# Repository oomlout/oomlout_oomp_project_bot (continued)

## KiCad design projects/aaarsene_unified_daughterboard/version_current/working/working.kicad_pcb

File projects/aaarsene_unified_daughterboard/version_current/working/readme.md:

# OOMP Project  
## Unified-Daughterboard  by aaarsene  
  
oomp key: oomp_projects_flat_aaarsene_unified_daughterboard  
(snippet of original readme)  
  
- Unified Daughterboard Project  

-- Introduction  
The Unified Daughterboard Project is an attempt by leading designers in the mechanical keyboard community to standardize the USB daughterboards used for their custom mechanical keyboard projects. It has initially been envisioned by users ai03, Wilba, Hineybush, Xelus, Xondat, aeryxz and Maximillian.  
  
The main characteristic of this daughterboard is to integrate a USB Type C connector and the needed circuitry for USB2.0 operation in a small PCB that can be screwed to a keyboard chassis; this significantly simplifies the assembly and design of the main circuit board.  
  
-- C3 version  
  
In its latest version, C3, this daughterboard features:  
  
* ESD (Electrostatic Discharge) protection on the data lines of the USB connector through a specialized chip;  
* Overcurrent protection through a PTC fuse;  
* Overvoltage protection through a bidirectional TVS diode;  
* Shielding noise decoupling capabilities through a ferrite bead;  
* Single-path grounding of the metallic chassis to which the daughterboard is attached.  
  
Adittionally, the C3 version is backwards compatible with both C1 and C2 versions since it has the same dimensions and us  
  full source readme at [readme_src.md](readme_src.md)  
  
source repo at: [https://github.com/aaarsene/Unified-Daughterboard](https://github.com/aaarsene/Unified-Daughterboard)  
## Board  

## Schematic  

[schematic pdf](working_schematic.pdf)  
## Images

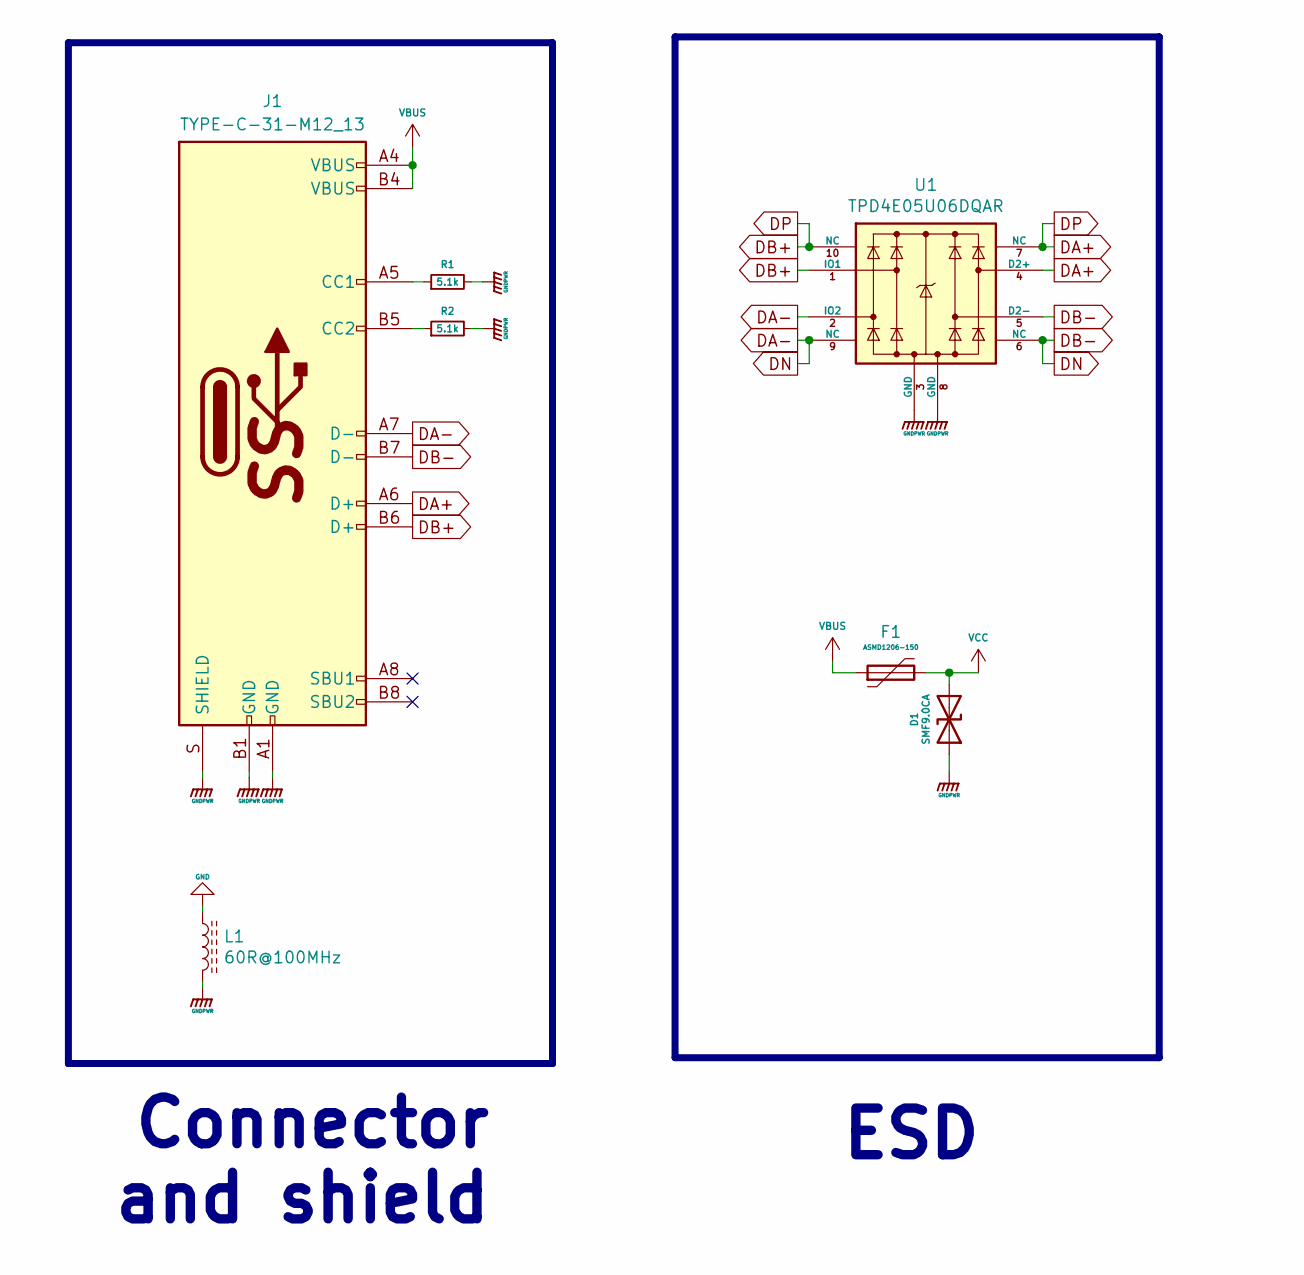
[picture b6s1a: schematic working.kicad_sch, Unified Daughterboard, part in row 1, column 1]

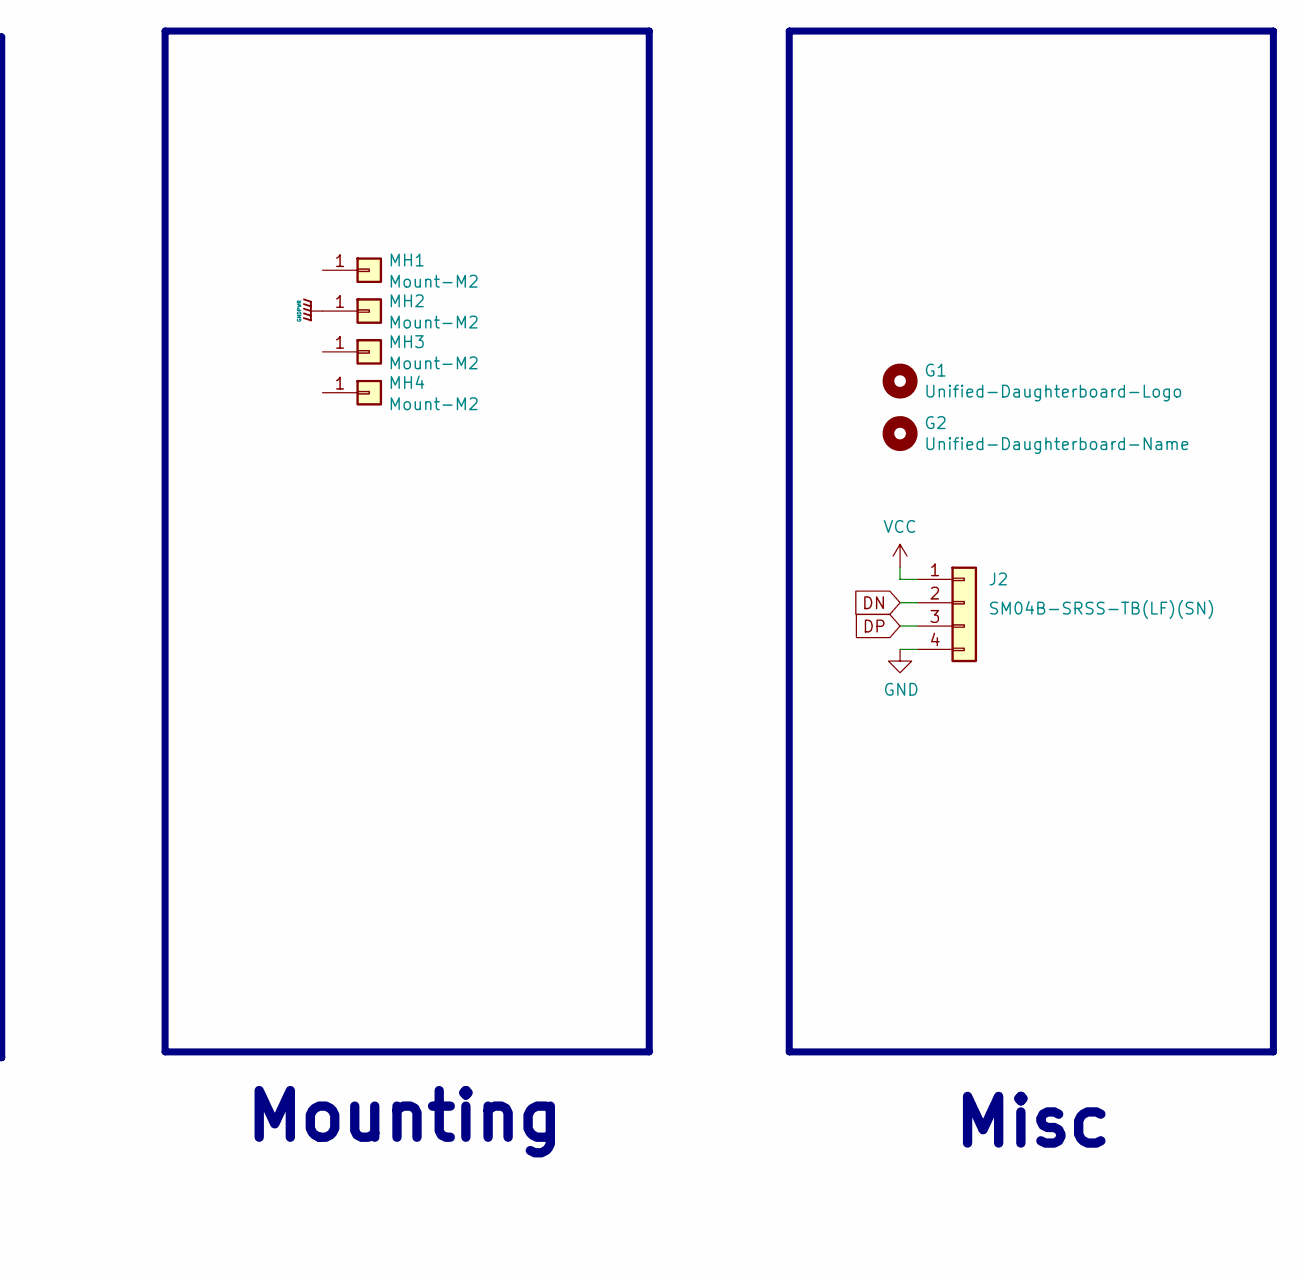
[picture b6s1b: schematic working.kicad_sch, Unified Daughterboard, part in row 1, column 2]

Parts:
D1: SMF9.0CA; D_SOD-123_Bidirectional; Manufacturer Part No SMF9.0CA; LCSC Part No C123799
F1: ASMD1206-150; Fuse_1206_3216Metric; Manufacturer Part No ASMD1206-150; LCSC Part No C135342
G1: Unified-Daughterboard-Logo; Unified-Daughterboard-Logo.pretty
G2: Unified-Daughterboard-Name; Unified-Daughterboard-Name.pretty
J1: TYPE-C-31-M12_13; TYPE-C-31-M-12; Manufacturer Part No TYPE-C-31-M-12; LCSC Part No C165948
J2: SM04B-SRSS-TB(LF)(SN); JST-SR-4; Manufacturer Part No SM04B-SRSS-TB(LF)(SN); LCSC Part No C160404
L1: 60R@100MHz; L_1206_3216Metric; Manufacturer Part No MLB3216-600P4A(f); LCSC Part No C33600
MH1, MH2, MH3, MH4: Mount-M2; Generic-Mounthole
R1, R2: 5.1k; R_0603
U1: TPD4E05U06DQAR; USON-10_2.5x1.0mm_P0.5mm; Manufacturer Part No TPD4E05U06DQAR; LCSC Part No C138714

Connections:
DA+: J1.A6 (D+), J1.B6 (D+), J2.3, U1.1 (IO1), U1.4 (D2+), U1.7 (NC), U1.10 (NC)
DA-: J1.A7 (D-), J1.B7 (D-), J2.2, U1.2 (IO2), U1.5 (D2-), U1.6 (NC), U1.9 (NC)
GND: J2.4, L1.1
GNDPWR: D1.1 (A1), J1.A1 (GND), J1.B1 (GND), J1.S (SHIELD), L1.2, MH2.1, R1.2, R2.2, U1.3 (GND), U1.8 (GND)
unnamed: J1.A5 (CC1), R1.1
unnamed: J1.B5 (CC2), R2.1
VBUS: F1.1, J1.A4 (VBUS), J1.B4 (VBUS)
VCC: D1.2 (A2), F1.2, J2.1

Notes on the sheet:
ESD
Misc
Connector and shield
Mounting

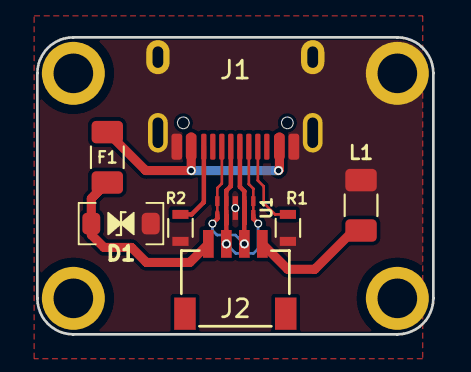
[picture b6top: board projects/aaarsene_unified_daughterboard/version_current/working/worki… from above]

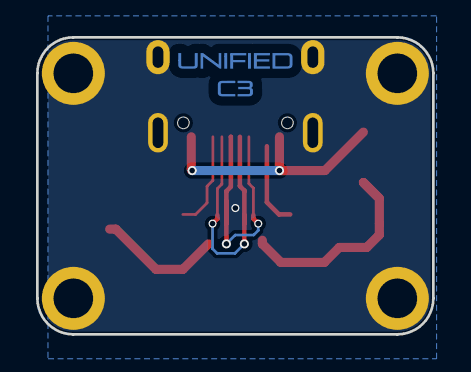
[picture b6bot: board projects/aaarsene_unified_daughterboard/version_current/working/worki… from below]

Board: 2 copper layers, 22.0 x 16.5 mm, 14 parts (2 on the bottom side), 8 nets.

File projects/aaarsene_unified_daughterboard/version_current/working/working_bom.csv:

"Id";"Designator";"Footprint";"Quantity";"Designation";"Supplier and ref";
1;"J1";"TYPE-C-31-M-12";1;"TYPE-C-31-M12_13";;;
2;"J2";"JST-SR-4";1;"SM04B-SRSS-TB(LF)(SN)";;;
3;"D1";"D_SOD-123_Bidirectional";1;"SMF9.0CA";;;
4;"F1";"Fuse_1206_3216Metric";1;"ASMD1206-150";;;
5;"U1";"USON-10_2.5x1.0mm_P0.5mm";1;"TPD4E05U06DQAR";;;
6;"R2,R1";"R_0603";2;"5.1k";;;
7;"L1";"L_1206_3216Metric";1;"60R@100MHz";;;
8;"G2";"Unified-Daughterboard-Name.pretty";1;"Unified-Daughterboard-Name";;;
9;"G1";"Unified-Daughterboard-Logo.pretty";1;"Unified-Daughterboard-Logo";;;

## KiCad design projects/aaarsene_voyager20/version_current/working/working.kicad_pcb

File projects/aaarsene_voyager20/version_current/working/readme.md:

# OOMP Project  
## Voyager20  by aaarsene  
  
oomp key: oomp_projects_flat_aaarsene_voyager20  
(snippet of original readme)  
  
- Voyager20  
A versatile, modern numpad PCB  
  
This is the 24 key variant with fn row.  
For the regular variant, see [this](https://github.com/ai03-2725/Voyager20).  

---- In light of recent claims that I am 100% liable for any of my open source PCBs, I am adding this disclaimer.  
---- I provide these PCBs as a reference for designing keyboard PCBs. Using them within your projects will require a will to do research of one's own and to learn the workings of them, potentially fixing issues if they exist.  
- I provide these PCBs without liability and without any guarantees regarding functionality, as expressed in the MIT license under which all of these PCBs are licensed.  
  
--- Features  
* In-switch LED backlighting  
* RGB underglow  
* Decent amount of layout compatibility - 2U positions can be replaced with 2x1U keys  
* Over-current and static discharge protection  
* Fully open-source  
  
--- The Voyager PCB Family  
The Voyager PCBs offer fully featured PCBs fit for any keyboard, whether mass production or high-end.  
  
  full source readme at [readme_src.md](readme_src.md)  
  
source repo at: [https://github.com/aaarsene/Voyager20](https://github.com/aaarsene/Voyager20)  
## Board  

## Schematic  

[schematic pdf](working_schematic.pdf)  
## Images

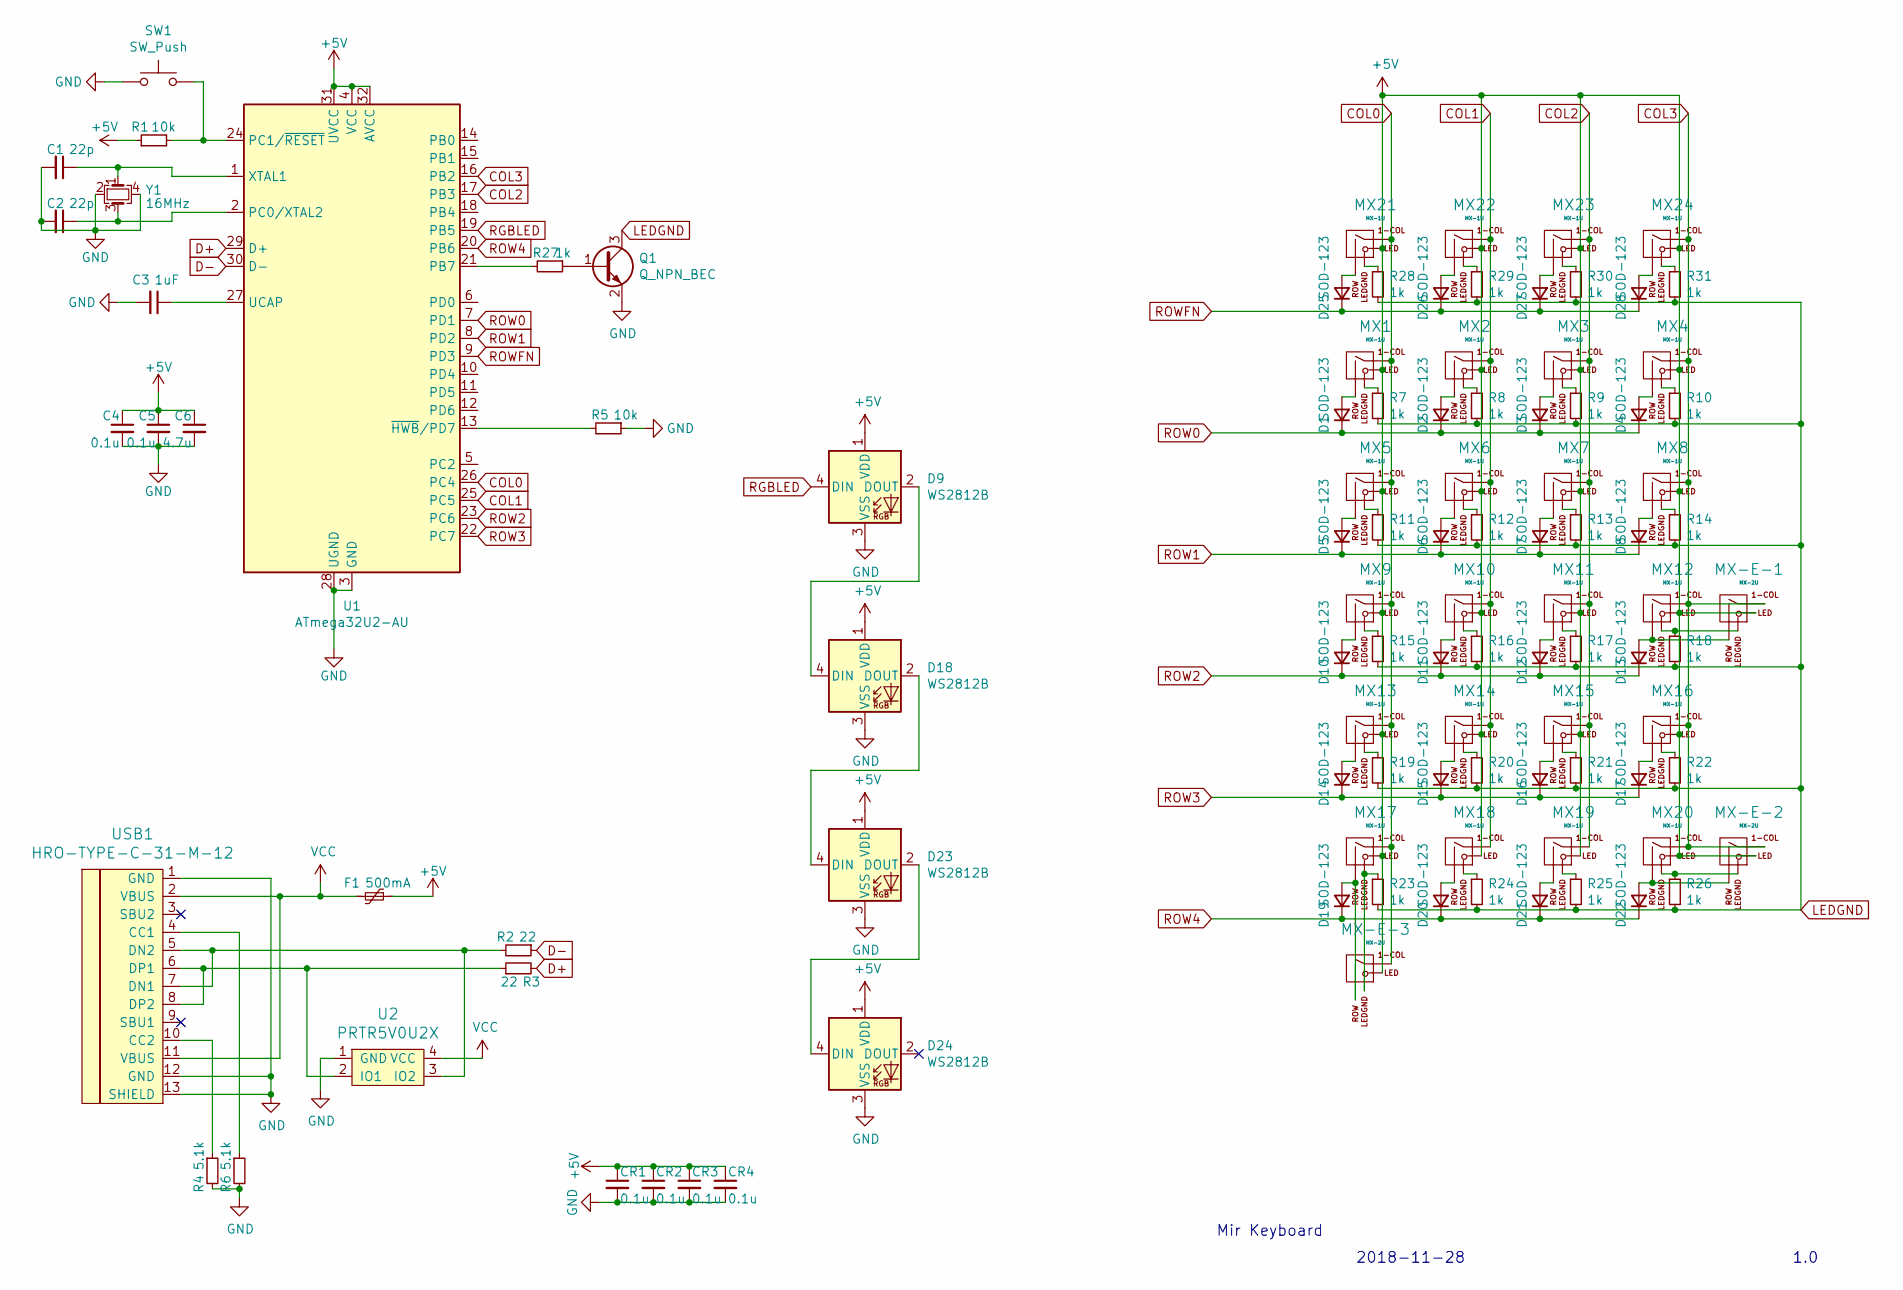
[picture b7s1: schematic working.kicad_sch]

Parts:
C1, C2: 22p; C_0603_1608Metric
C3: 1uF; C_0603_1608Metric
C4, C5: 0.1u; C_0603_1608Metric
C6: 4.7u; C_0603_1608Metric
CR1, CR2, CR3, CR4: 0.1u; C_0603_1608Metric
D1, D2, D3, D4, D5, D6, D7, D8, D10, D11, D12, D13, D14, D15, D16, D17, D19, D20, D21, D22, D25, D26, D27, D28: SOD-123; D_SOD-123
D9, D18, D23, D24: WS2812B; LED_WS2812B_PLCC4_5.0x5.0mm_P3.2mm
F1: 500mA; Fuse_1206_3216Metric
MX1, MX2, MX3, MX4, MX5, MX6, MX7, MX8, MX9, MX10, MX11, MX12, MX13, MX14, MX15, MX16, MX17, MX18, MX19, MX20, MX21, MX22, MX23, MX24: MX-1U
MX-E-1, MX-E-2, MX-E-3: MX-2U; MX-2U-ReversedStabilizers
Q1: Q_NPN_BEC; SOT-23
R1, R5: 10k; R_0805_2012Metric
R2, R3: 22; R_0805_2012Metric
R4, R6: 5.1k; R_0805_2012Metric
R7, R8, R9, R10, R11, R12, R13, R14, R15, R16, R17, R18, R19, R20, R21, R22, R23, R24, R25, R26, R27, R28, R29, R30, R31: 1k; R_0805_2012Metric
SW1: SW_Push; SKQG-1155865
U1: ATmega32U2-AU; QFN-32-1EP_5x5mm_P0.5mm_EP3.65x3.65mm
U2: PRTR5V0U2X; SOT143B
USB1: HRO-TYPE-C-31-M-12; HRO-TYPE-C-31-M-12-Assembly
Y1: 16MHz; Crystal_SMD_3225-4Pin_3.2x2.5mm

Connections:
+5V: C4.1, C5.1, C6.1, CR1.1, CR2.1, CR3.1, CR4.1, D9.1 (VDD), D18.1 (VDD), D23.1 (VDD), D24.1 (VDD), F1.1, MX1.3 (LED), MX2.3 (LED), MX3.3 (LED), MX4.3 (LED), MX5.3 (LED), MX6.3 (LED), MX7.3 (LED), MX8.3 (LED), MX9.3 (LED), MX10.3 (LED), MX11.3 (LED), MX12.3 (LED), MX13.3 (LED), MX14.3 (LED), MX15.3 (LED), MX16.3 (LED), MX17.3 (LED), MX18.3 (LED), MX19.3 (LED), MX20.3 (LED), MX21.3 (LED), MX22.3 (LED), MX23.3 (LED), MX24.3 (LED), MX-E-1.3 (LED), MX-E-2.3 (LED), MX-E-3.3 (LED), R1.1, U1.4 (VCC), U1.31 (UVCC), U1.32 (AVCC)
COL0: MX1.1 (COL), MX5.1 (COL), MX9.1 (COL), MX13.1 (COL), MX17.1 (COL), MX21.1 (COL), MX-E-3.1 (COL), U1.26 (PC4)
COL1: MX2.1 (COL), MX6.1 (COL), MX10.1 (COL), MX14.1 (COL), MX18.1 (COL), MX22.1 (COL), U1.25 (PC5)
COL2: MX3.1 (COL), MX7.1 (COL), MX11.1 (COL), MX15.1 (COL), MX19.1 (COL), MX23.1 (COL), U1.17 (PB3)
COL3: MX4.1 (COL), MX8.1 (COL), MX12.1 (COL), MX16.1 (COL), MX20.1 (COL), MX24.1 (COL), MX-E-1.1 (COL), MX-E-2.1 (COL), U1.16 (PB2)
D+: R3.2, U1.29 (D+)
D-: R2.1, U1.30 (D-)
GND: C1.2, C2.2, C3.2, C4.2, C5.2, C6.2, CR1.2, CR2.2, CR3.2, CR4.2, D9.3 (VSS), D18.3 (VSS), D23.3 (VSS), D24.3 (VSS), Q1.2 (E), R4.2, R5.1, R6.2, SW1.1, U1.3 (GND), U1.28 (UGND), U2.1 (GND), USB1.1 (GND), USB1.12 (GND), USB1.13 (SHIELD), Y1.2, Y1.4
LEDGND: Q1.3 (C), R7.2, R8.2, R9.2, R10.2, R11.2, R12.2, R13.2, R14.2, R15.2, R16.2, R17.2, R18.2, R19.2, R20.2, R21.2, R22.2, R23.2, R24.2, R25.2, R26.2, R28.2, R29.2, R30.2, R31.2
unnamed: C1.1, U1.1 (XTAL1), Y1.1
unnamed: C2.1, U1.2 (PC0/XTAL2), Y1.3
unnamed: C3.1, U1.27 (UCAP)
unnamed: D1.2 (A), MX1.2 (ROW)
unnamed: D2.2 (A), MX2.2 (ROW)
unnamed: D3.2 (A), MX3.2 (ROW)
unnamed: D4.2 (A), MX4.2 (ROW)
unnamed: D5.2 (A), MX5.2 (ROW)
unnamed: D6.2 (A), MX6.2 (ROW)
unnamed: D7.2 (A), MX7.2 (ROW)
unnamed: D8.2 (A), MX8.2 (ROW)
unnamed: D10.2 (A), MX9.2 (ROW)
unnamed: D11.2 (A), MX10.2 (ROW)
unnamed: D12.2 (A), MX11.2 (ROW)
unnamed: D13.2 (A), MX12.2 (ROW), MX-E-1.2 (ROW)
unnamed: D14.2 (A), MX13.2 (ROW)
unnamed: D15.2 (A), MX14.2 (ROW)
unnamed: D16.2 (A), MX15.2 (ROW)
unnamed: D17.2 (A), MX16.2 (ROW)
unnamed: D18.2 (DOUT), D23.4 (DIN)
unnamed: D9.2 (DOUT), D18.4 (DIN)
unnamed: D19.2 (A), MX17.2 (ROW), MX-E-3.2 (ROW)
unnamed: D20.2 (A), MX18.2 (ROW)
unnamed: D21.2 (A), MX19.2 (ROW)
unnamed: D22.2 (A), MX20.2 (ROW), MX-E-2.2 (ROW)
unnamed: D23.2 (DOUT), D24.4 (DIN)
unnamed: D25.2 (A), MX21.2 (ROW)
unnamed: D26.2 (A), MX22.2 (ROW)
unnamed: D27.2 (A), MX23.2 (ROW)
unnamed: D28.2 (A), MX24.2 (ROW)
unnamed: MX1.4 (LEDGND), R7.1
unnamed: MX2.4 (LEDGND), R8.1
unnamed: MX3.4 (LEDGND), R9.1
unnamed: MX4.4 (LEDGND), R10.1
unnamed: MX5.4 (LEDGND), R11.1
unnamed: MX6.4 (LEDGND), R12.1
unnamed: MX7.4 (LEDGND), R13.1
unnamed: MX8.4 (LEDGND), R14.1
unnamed: MX9.4 (LEDGND), R15.1
unnamed: MX10.4 (LEDGND), R16.1
unnamed: MX11.4 (LEDGND), R17.1
unnamed: MX13.4 (LEDGND), R19.1
unnamed: MX14.4 (LEDGND), R20.1
unnamed: MX15.4 (LEDGND), R21.1
unnamed: MX16.4 (LEDGND), R22.1
unnamed: MX18.4 (LEDGND), R24.1
unnamed: MX19.4 (LEDGND), R25.1
unnamed: MX21.4 (LEDGND), R28.1
unnamed: MX22.4 (LEDGND), R29.1
unnamed: MX23.4 (LEDGND), R30.1
unnamed: MX24.4 (LEDGND), R31.1
unnamed: MX12.4 (LEDGND), MX-E-1.4 (LEDGND), R18.1
unnamed: MX20.4 (LEDGND), MX-E-2.4 (LEDGND), R26.1
unnamed: MX17.4 (LEDGND), MX-E-3.4 (LEDGND), R23.1
unnamed: Q1.1 (B), R27.1
unnamed: R1.2, SW1.2, U1.24 (PC1/~RESET)
unnamed: R2.2, U2.3 (IO2), USB1.5 (DN2), USB1.7 (DN1)
unnamed: R3.1, U2.2 (IO1), USB1.6 (DP1), USB1.8 (DP2)
unnamed: R4.1, USB1.10 (CC2)
unnamed: R5.2, U1.13 (~HWB/PD7)
unnamed: R6.1, USB1.4 (CC1)
unnamed: R27.2, U1.21 (PB7)
RGBLED: D9.4 (DIN), U1.19 (PB5)
ROW0: D1.1 (K), D2.1 (K), D3.1 (K), D4.1 (K), U1.7 (PD1)
ROW1: D5.1 (K), D6.1 (K), D7.1 (K), D8.1 (K), U1.8 (PD2)
ROW2: D10.1 (K), D11.1 (K), D12.1 (K), D13.1 (K), U1.23 (PC6)
ROW3: D14.1 (K), D15.1 (K), D16.1 (K), D17.1 (K), U1.22 (PC7)
ROW4: D19.1 (K), D20.1 (K), D21.1 (K), D22.1 (K), U1.20 (PB6)
ROWFN: D25.1 (K), D26.1 (K), D27.1 (K), D28.1 (K), U1.9 (PD3)
VCC: F1.2, U2.4 (VCC), USB1.2 (VBUS), USB1.11 (VBUS)

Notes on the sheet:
2018-11-28
1.0
Mir Keyboard

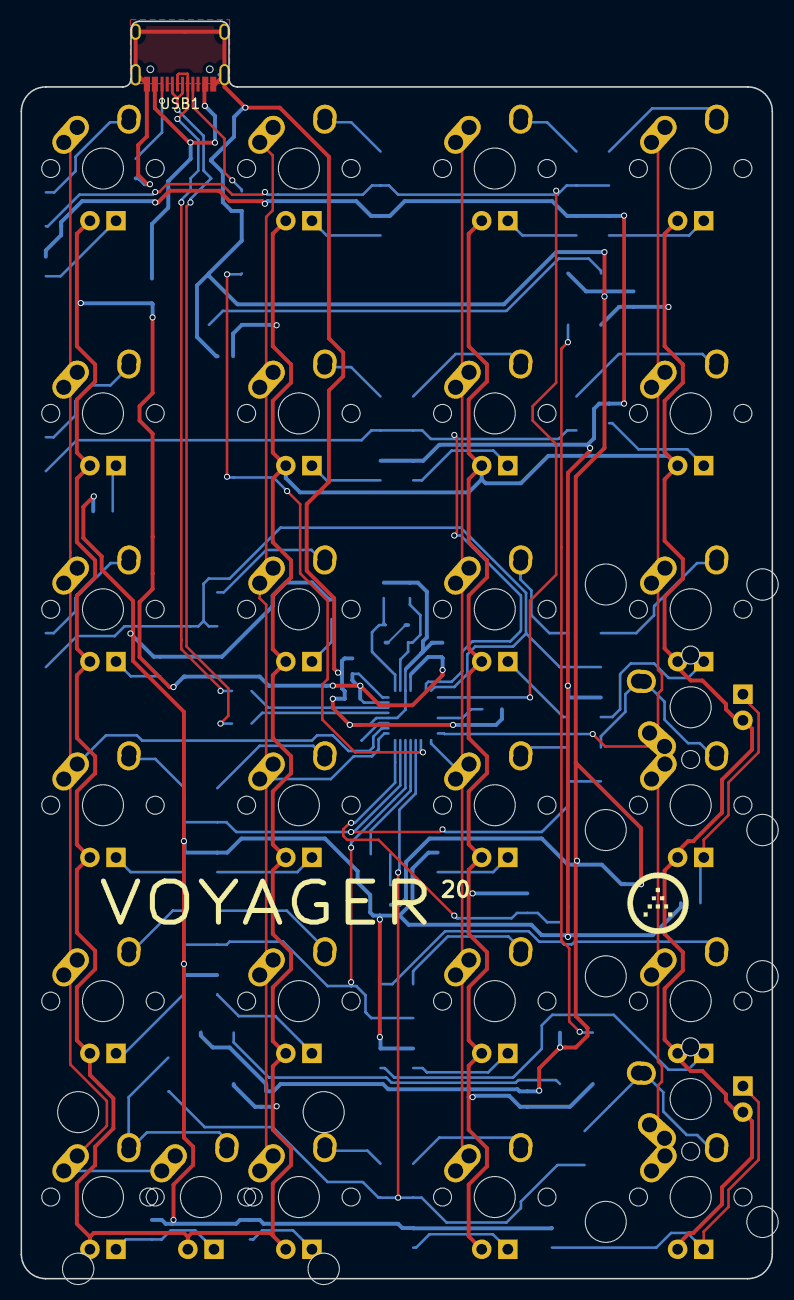
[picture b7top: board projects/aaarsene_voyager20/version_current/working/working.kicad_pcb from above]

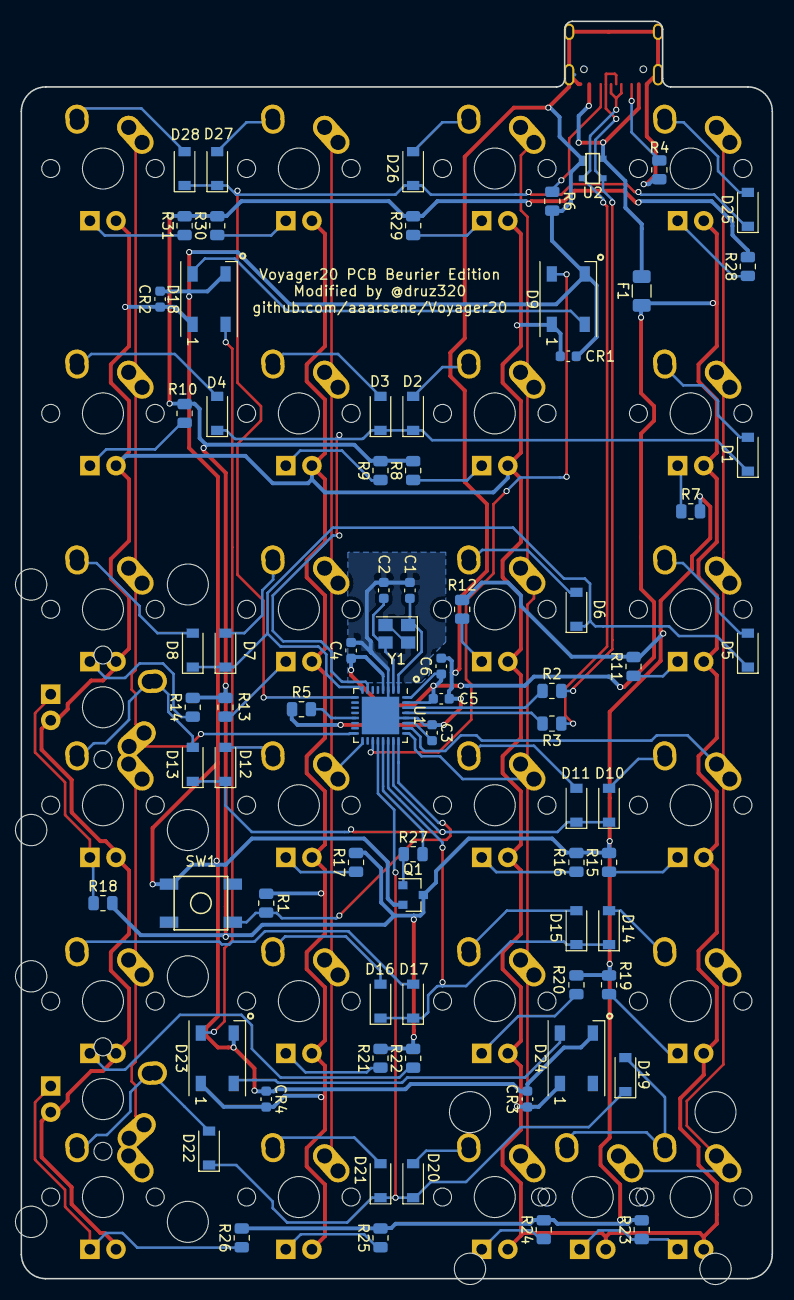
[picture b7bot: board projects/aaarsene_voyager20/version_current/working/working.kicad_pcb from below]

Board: 2 copper layers, 73.0 x 122.3 mm, 103 parts (75 on the bottom side), 79 nets.

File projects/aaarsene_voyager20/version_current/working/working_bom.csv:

"Id";"Designator";"Footprint";"Quantity";"Designation";"Supplier and ref";
1;"F1";"Fuse_1206_3216Metric";1;"500mA";;;
2;"Y1";"Crystal_SMD_3225-4Pin_3.2x2.5mm";1;"16MHz";;;
3;"U1";"QFN-32-1EP_5x5mm_P0.5mm_EP3.65x3.65mm";1;"ATmega32U2-AU";;;
4;"R31,R30,R29,R28,R27,R26,R25,R24,R23,R22,R21,R20,R19,R18,R17,R16,R15,R14,R13,R12,R11,R10,R9,R8,R7";"R_0805_2012Metric";25;"1k";;;
5;"R6,R4";"R_0805_2012Metric";2;"5.1k";;;
6;"R5,R1";"R_0805_2012Metric";2;"10k";;;
7;"R3,R2";"R_0805_2012Metric";2;"22";;;
8;"Q1";"SOT-23";1;"Q_NPN_BEC";;;
9;"D28,D27,D26,D25,D22,D21,D20,D19,D17,D16,D15,D14,D13,D12,D11,D10,D8,D7,D6,D5,D4,D3,D2,D1";"D_SOD-123";24;"SOD-123";;;
10;"D24,D23,D18,D9";"LED_WS2812B_PLCC4_5.0x5.0mm_P3.2mm";4;"WS2812B";;;
11;"C1,C2";"C_0603_1608Metric";2;"22p";;;
12;"C3";"C_0603_1608Metric";1;"1uF";;;
13;"C4,C5,CR1,CR2,CR3,CR4";"C_0603_1608Metric";6;"0.1u";;;
14;"C6";"C_0603_1608Metric";1;"4.7u";;;
15;"MX1,MX2,MX3,MX4,MX5,MX6,MX7,MX8,MX9,MX10,MX11,MX12,MX13,MX14,MX15,MX16,MX17,MX18,MX19,MX20,MX21,MX22,MX23,MX24";"MX-1U";24;"MX-1U";;;
16;"SW1";"SKQG-1155865";1;"SW_Push";;;
17;"U2";"SOT143B";1;"PRTR5V0U2X";;;
18;"USB1";"HRO-TYPE-C-31-M-12-Assembly";1;"HRO-TYPE-C-31-M-12";;;
19;"MX-E-1,MX-E-2,MX-E-3";"MX-2U-ReversedStabilizers";3;"MX-2U";;;
20;"G***";"ai-ring-6mm";1;"LOGO";;;
